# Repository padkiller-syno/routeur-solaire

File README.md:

# Routeur solaire — ESPHome sur ESP32 DevKit V1

Portage du routeur Profes'Solaire v9.15 (`esp32_oled_ac_v9_15.ino`) sur un **ESP32 DevKit V1**
(ESP-WROOM-32) sous **ESPHome**, relié à Home Assistant par l'API native. But : envoyer le surplus solaire dans le
ballon d'eau chaude, et garantir de l'eau chaude le soir.

- Gardé : JSY-MK-194T, **2 dimmers** (même table de pas que la v9.15), relais surplus (sortie 3), relais de marche
  forcée, sonde DS18B20 du ballon (désormais déportée en 433 MHz, voir `sonde-433/`).
- Ajouté : sonde DS18B20 de sécurité sur le radiateur des triacs, détection « ballon chaud », seuils du relais réglables
  depuis HA, anti-légionelle, marche forcée de secours si HA est injoignable.
- Retiré : écran OLED, page web ESP-DASH, topics MQTT `mosquitto/...`, relais Bluetooth (routeur dédié au routage).
- **Deux cœurs** : wifi et pile réseau sur le cœur 0 ; boucle ESPHome (JSY, régulation) sur le cœur 1 ;
  triacs pilotés par une interruption de minuterie matérielle.
- Les marches forcées sont faites par des **automatisations Home Assistant** qui lisent les réglages de l'ESP.

Fichiers :
- `esphome/routeur-solaire.yaml` : configuration ESPHome.
- `esphome/routeur-solaire/routeur.h` : décodage du JSY (avec contrôle du CRC Modbus) et table des pas.
- `test/test_routeur.c` : test hors carte de `routeur.h` (`gcc -Wall -o /tmp/t test/test_routeur.c -lm && /tmp/t`).
- `cablage.svg` : schéma de câblage basse tension (ESP, modules, 3,3 V / 5 V / masse).
- `ha-carte-solaire-ecs.yaml` : carte pour la page « Solaire ECS » de HA (coller en carte « Manuel »).
- `outils/vitesse_port_jsy.ino` : passage du JSY de 4 800 à 38 400 bauds (une seule fois, depuis un ESP32).
- `puissance.svg` : schéma de la partie 230 V (tableau, boîtier près du ballon, contacteur, dimmer, ballon).
- `pcb/` : carte mère KiCad générée par script, fichiers de fabrication JLCPCB (voir `pcb/README-pcb.md`).
- `boitier/` : boîtier imprimé 3D OpenSCAD + STL (voir `boitier/README.md`).

Compilé avec ESPHome 2026.10.2 : RAM ≈ 28 %, flash ≈ 49 %. Premier flash : *⋮ → Install → Manual download → Factory format* dans ESPHome, puis
`esptool --chip esp32 --port /dev/ttyUSB0 --baud 460800 write_flash 0x0 routeur-solaire.factory.bin`
(esptool 4.x d'Ubuntu ; Firefox ne sait pas flasher en USB). Ensuite, mises à jour par le wifi.

## Câblage

| Signal | DevKit V1 | GPIO | Remarque |
|---|---|---|---|
| TX du JSY | RX2 | 16 | UART2 matérielle, pont diviseur R1/R2 sur la carte |
| RX du JSY | TX2 | 17 | |
| Z-C (dimmer 1) | D35 | 35 | entrée seule ; commun aux deux dimmers, Z-C du dimmer 2 non branché |
| PWM dimmer 1 (ballon) | D32 | 32 | |
| PWM dimmer 2 (option) | D33 | 33 | 2e charge ; activer « Sortie 2 active » dans HA |
| Relais marche forcée | D25 | 25 | NC → bobine du contacteur |
| Relais surplus | D26 | 26 | |
| Récepteur 433 MHz SRX882 (DATA) | D4 | 4 | bornier J2 ; reçoit la sonde déportée du ballon (`sonde-433/`) |
| DS18B20 triacs (DAT) | D27 | 27 | bus séparé, bornier J3 |
| Ventilateur 5 V des dimmers | D13 | 13 | MOSFET Q1 de la carte : marche au seuil (45 °C, réglable), arrêt 7 °C plus bas, forcé si la sonde des triacs se tait |

- Aucune broche de démarrage (0, 2, 5, 12, 15) n'est utilisée : rien ne s'active au boot ni pendant un flash USB.
- Les logs passent par le port USB (UART0) et le tableau de bord ESPHome ; le JSY a sa propre UART.
- La sonde des triacs a son propre fil : une panne sur un bus ne fait pas perdre l'autre sonde.
- TX du JSY → RX2 par le pont diviseur de la carte, 1 kΩ (R1, en série) / 2 kΩ (R2, vers la masse) : 5 V × 2/3 = 3,3 V.
  Si le TX du JSY sort déjà du 3,3 V (le mesurer au repos), remplacer R1 par un pont de soudure et retirer R2.
- 5 V : alimentation Mean Well IRM-05-5 dans le boîtier → bornier J4 de la carte → VIN de l'ESP, JSY, relais, ventilateur.
  3,3 V (dimmers, sondes) pris sur la broche 3V3 de l'ESP ; masse commune.

### Matériel

- **JSY-MK-194T déjà passé à 38 400 bauds** par `outils/vitesse_port_jsy.ino` (croquis ESP32 : requête Modbus en
  diffusion, registre 0x0004 = 0x0108, soit adresse 1 et code vitesse 8 = 38 400). C'est la vitesse et l'adresse
  qu'attend ESPHome ; c'est aussi la vitesse maximale du JSY, à garder (≈ 18 ms par échange, contre ≈ 144 ms à
  4 800 bauds, plus que le cycle de 120 ms). Un JSY neuf ou remis à zéro est à 4 800 bauds : bouton
  « JSY : passer à 38 400 bauds » dans HA (diagnostics de l'appareil, **masqué par défaut** : l'activer d'abord). Il
  coupe le dimmer, envoie la trame de réglage à 4 800 puis à 9 600 bauds, revient à 38 400 et écrit dans les logs si
  les mesures sont revenues. Le croquis reste utile sans ESPHome.
- **JSY-MK-194T** : broches VCC, RX, TX, PF, GND (PF non branchée). Canal 1 = tore intégré, à faire traverser par le fil
  du ballon ; canal 2 = pince externe sur l'arrivée générale ; UL/NL = 230 V pour la mesure de tension.
- **Sonde DS18B20 des triacs** (VCC, DAT, GND) sur le bornier J3, en 3,3 V : la résistance de tirage 4,7 kΩ est sur la
  carte (R4), ne pas en ajouter.
- **Sonde du ballon déportée** : le routeur est près du tableau, à ~10 m du ballon, et 10 m de câble 1-Wire le long de
  l'alimentation du ballon donnent des lectures fausses. Elle est lue sur place par un Pro Mini sur 18650 qui l'envoie en
  433 MHz (`sonde-433/README.md`). Récepteur **SRX882** sur J2 : VCC → 3,3 V, DATA → DAT, GND, **CS → 3,3 V**, antenne
  de 17,3 cm hors du tableau métallique. Entités `Batterie sonde ballon` et `Sonde ballon` (connectivité).
- **Ballon : 8 A (≈ 1 850 W)**, circuit dédié au tableau : différentiel 30 mA → disjoncteur 16 A → câble 3G 2,5 mm²
  jusqu'au ballon. Raccordement par une sortie de câble puis les presse-étoupes du boîtier, **pas de prise** (une prise
  chauffe sous une charge résistive de plusieurs heures par jour).
- **Relais : modules 5 V 10 A à déclenchement bas** (Songle SRD-05VDC-SL-C, broches IN / GND / VCC, bobine ≈ 70 mA),
  enfichés sur K1 (marche forcée) et K2 (surplus).
  - Relais surplus : contact NO vers une charge annexe de 2 kW au plus (au-delà, passer par un contacteur).
  - Relais marche forcée : il ne coupe pas le ballon lui-même, il pilote la **bobine du contacteur** par son
    contact **NC** : COM ← L, NC → A1 du contacteur, A2 → N. ESP éteint ou en panne = relais au repos = contacteur
    collé = ballon en direct sur son thermostat. En routage, la bobine du petit relais est alimentée en permanence.
  - Réglages pour ces modules, à poser dans `substitutions` au montage : `relais_surplus_inverse: "true"`,
    `relais_mf_inverse: "false"` (le fichier a encore les valeurs d'un module à déclenchement haut, l'inverse).
  - **Piège** : alimentés en 5 V, ces modules peuvent ne pas décoller avec les 3,3 V de l'ESP (pour leur transistor,
    3,3 V est encore un niveau bas). Test au banc avant montage : IN à la masse → le relais colle ; IN en l'air → il
    doit décoller franchement. S'il reste collé avec la broche de l'ESP à 3,3 V : passer les sorties en `open_drain`,
    ou souder une diode 1N4148 en série sur IN (cathode côté ESP).
- **Contacteur jour/nuit AEG 666120** (20 A, 2 NO, bobine 230 V, commutateur 0 / AUTO / 1) : sur rail DIN près du
  ballon. Son contact de puissance relie L à la phase du ballon, en parallèle de la sortie LOAD du dimmer : en marche
  forcée, le triac est court-circuité. Commutateur sur **AUTO** ; **1** = marche forcée manuelle, même ESP en panne ;
  **0** = ballon coupé.
- **Pince du canal 2 (arrivée générale), rallongée jusqu'au tableau** — le boîtier est près du ballon :
  - Câble : **H05VV-F 2 × 0,75 mm²** (isolé 300/500 V), torsadé à la main (un tour tous les 5 à 10 cm), ou sa version
    blindée (blindage relié à la masse côté JSY seulement). Une pince à sortie courant supporte sans souci 10 à 20 m.
  - Passage : dans la même gaine ICTA que le câble du ballon, ou fixé le long d'elle. Les fils de la pince sont reliés
    au circuit de mesure du JSY, référencé au secteur : les traiter comme du 230 V (pas de câble Ethernet).
  - Raccord : souder et gainer (thermorétractable), ou bornier dans une boîte ; garder la fiche d'origine côté JSY.
  - **Ne jamais laisser la pince fermée sur un câble sous tension avec ses fils débranchés** (secondaire de
    transformateur de courant ouvert = tension élevée, pince abîmée) : brancher d'abord la rallonge, puis clipser.
  - Pose : autour de la **phase seule** de l'arrivée générale, après le compteur et avant tous les départs.
    Flèche de la pince dans le sens compteur → maison.
  - Contrôle : la nuit (aucune production), `Puissance réseau` doit être **positive** dans HA. Si elle est
    négative, retourner la pince.
- **Alimentation 5 V** : Mean Well IRM-05-5 (5 V 1 A, classe II) dans le boîtier, derrière un fusible **T1A** temporisé
  sur la phase (porte-fusible de façade 250 V) ; le même fusible protège les fils L/N du JSY. Sortie sur J4 (bornier
  débrochable 2 points, pas de 3,5 mm), protégée sur la carte par F1 (PTC 1,1 A) et D2. ≈ 0,6 A en pointe (ESP32 avec
  wifi, JSY, 2 relais, ventilateur). Le micro-USB de l'ESP ne sert plus qu'au premier flash.
- **Dimmer RobotDyn « AC Dimmer Module HL » 16/24 A 600 V** : logique VCC (3,3 V),
  GND, Z-C → D35, PWM → D32 (dimmer 2 : PWM → D33, Z-C libre). Puissance : AC-IN **L** et **N**, sortie **LOAD** vers la phase du ballon ; l'autre fil du
  ballon va directement au neutre. Avec un ballon de 8 A, la version 16 A est à l'aise (≈ 10 W dans le triac) ;
  radiateur à l'air libre, sonde DS18B20 « triacs » collée (pâte ou colle thermique) sur le peigne en aluminium, au plus
  près du triac (avec deux dimmers : sur celui qui chauffe le plus, ou les deux radiateurs serrés l'un contre l'autre).
- Sonde du ballon : en partie haute (doigt de gant ou contre la cuve sous l'isolant), c'est l'eau qui sort au robinet.

## Installation

1. Copier `esphome/routeur-solaire.yaml` et le dossier `esphome/routeur-solaire/` dans la configuration ESPHome.
2. Ajouter à `secrets.yaml` : `wifi_ssid`, `wifi_password`, `routeur_api_key` (clé de 32 octets en base64, par exemple
   `openssl rand -base64 32`) et `routeur_ota_password`.
3. Premier flash par USB (voir plus haut), puis mises à jour par le wifi.
4. Dans HA : *Paramètres → Appareils et services → Ajouter une intégration → ESPHome* (découverte automatique sur le
   même réseau, sinon par l'IP de l'ESP, port 6053), avec la clé d'API. Réserver l'IP de l'ESP dans le DHCP de la box.
5. Créer les automatisations de marche forcée (voir *Fonctionnement*) et le capteur `statistics`
   `sensor.ballon_temperature_max_7_jours` (max sur 7 jours de la température du ballon).
6. Carte de tableau de bord : *Ajouter une carte → Manuel* → coller `ha-carte-solaire-ecs.yaml`.

Réglages dans `substitutions` : `dimmer_max` (95 %), `mf_duree_max` (la marche forcée se coupe seule au bout de 8 h si
HA ne l'a pas fait), `triac_coupure` / `triac_reprise` (75 / 60 °C).

## Fonctionnement

**Routage** (dans l'ESP, toutes les 120 ms) : une consigne unique monte ou descend selon la puissance réseau pour
viser entre −30 et 0 W d'injection, avec la table de pas de la v9.15. De 0 à 95 % elle pilote le dimmer 1 (ballon) ;
au-delà, si « Sortie 2 active » est allumé, le dimmer 2 prend la suite jusqu'à 95 %. À la descente, le dimmer 2 baisse
d'abord, puis le dimmer 1 : pas d'à-coup (la v9.15 remettait la sortie 2 à zéro dès que la 1 quittait son maximum).
« Sortie 2 active » est éteint par défaut : ne l'allumer qu'avec une charge branchée sur le dimmer 2.
Le JSY ne rafraîchit ses mesures que toutes les 330 ms : la consigne n'est corrigée que sur une trame nouvelle
(la v9.15 appliquait le même pas 2 à 3 fois sur la même mesure). 5 s de trames identiques = JSY figé, traité comme muet
(dimmer coupé). Wifi coupé : l'ESP ne redémarre jamais et continue de router seul.

**Marche forcée de secours** : si HA est injoignable à l'heure réglée, l'ESP applique seul la règle « température »
(chauffe si l'eau est sous la consigne, arrêt dès qu'elle l'atteint), avec l'heure de HA ou à défaut l'heure Internet
(SNTP). Quand HA est là, l'ESP le laisse faire.

**Relais surplus** : collé quand surplus (injection + puissance du ballon) > « seuil marche », décollé sous
« seuil arrêt », au moins 60 s entre deux changements. Les deux seuils se règlent dans HA (1000 / 800 W par défaut) :
mettre le seuil de marche à peu près à la puissance de la charge branchée sur ce relais.

**Ballon chaud** : dimmer au maximum mais moins de 30 W dans le ballon pendant 60 s = thermostat du ballon ouvert.
`binary_sensor.sdb_routeur_solaire_ballon_chaud` passe à « on » (levé dès que le ballon reprend plus de 100 W). Le surplus
n'a alors plus que le relais surplus ; le capteur peut aussi servir dans HA (notification, lancer un appareil…).

**Sécurité triac** : radiateur ≥ 75 °C → dimmer coupé, reprise sous 60 °C. Sonde absente ou muette depuis 60 s →
dimmer coupé aussi (sûr par défaut : **sans cette sonde branchée, le routeur ne route pas**). La marche forcée n'est
pas concernée (elle passe par le contacteur, pas par le triac). `binary_sensor.sdb_routeur_solaire_securite_triac`
signale le problème.

**Marches forcées** (automatisations HA, à l'heure réglée sur l'ESP) :

| Automatisation | Quand | Arrêt |
|---|---|---|
| marche forcée température (activée par défaut) | à 16:00 si l'eau est sous 40 °C | dès que l'eau dépasse 40 °C |
| anti-légionelle | à 16:00 si l'eau n'a pas dépassé 60 °C depuis 7 jours | à 60 °C, ou au bout de 6 h |
| marche forcée volume (désactivée par défaut) | à l'heure réglée, si l'énergie routée du jour est sous le besoin du ballon (formules v9.15) | après la durée calculée |

- 16:00 et 40 °C sont les valeurs par défaut de l'ESP, modifiables dans HA ; elles servent à toutes les marches forcées.
- Pendant l'anti-légionelle, l'arrêt à 40 °C de la marche forcée température est suspendu.
- Le max sur 7 jours vient de `sensor.ballon_temperature_max_7_jours` (intégration `statistics`, `configuration.yaml`).
  Juste après la mise en service, il n'a que quelques heures d'historique : un premier cycle à 60 °C est normal.
- Sans sonde du ballon (aucune trame reçue depuis 5 min), ni marche forcée température ni anti-légionelle (la v9.15 lisait −127 °C et chauffait toutes
  les nuits).
- Si HA redémarre pendant une marche forcée volume ou anti-légionelle, l'arrêt est perdu : la sécurité de 8 h de l'ESP coupe.

## Entités Home Assistant

HA préfixe les entités par la pièce de l'appareil (ici `sdb_`, salle de bain) : adapter les noms ci-dessous, les
automatisations et la carte à votre installation.

**Commandes et réglages** (gardés dans la flash de l'ESP, ils survivent aux coupures) :

| Entité | Défaut | v9.15 |
|---|---|---|
| `switch.sdb_routeur_solaire_marche_forcee` | arrêt | bouton « Auto / Marche forcée » (inversé) |
| `switch.sdb_routeur_solaire_programmation_temperature` | marche | « Horloge On/Off température » |
| `switch.sdb_routeur_solaire_programmation_volume` | arrêt | « Horloge On/Off volume » |
| `time.sdb_routeur_solaire_heure_marche_forcee` | 16:00 | curseurs heure / minute |
| `number.sdb_routeur_solaire_temperature_marche_forcee` | 40 °C (10-90, pas de 5) | curseur température |
| `number.sdb_routeur_solaire_volume_ballon` | 200 L | `volume` dans le code |
| `number.sdb_routeur_solaire_relais_surplus_seuil_marche` | 1000 W | `relayOn` dans le code |
| `number.sdb_routeur_solaire_relais_surplus_seuil_arret` | 800 W | `relayOff` dans le code |

**Mesures** — elles remplacent les capteurs du bloc `mqtt:` (l'historique reste sur les anciennes entités) :

| Entité | Ancien capteur MQTT |
|---|---|
| `sensor.sdb_routeur_solaire_puissance_reseau` (W, > 0 soutirage, < 0 injection) | « Consommation » |
| `sensor.sdb_routeur_solaire_puissance_ballon` (W) | « Puissance surplus » |
| `sensor.sdb_routeur_solaire_energie_routee` (kWh, utilisable dans le tableau Énergie) | « Energie sauvée totale » |
| `sensor.sdb_routeur_solaire_energie_reseau_canal_2` (kWh) | « Consommation Enedis totale » |
| `sensor.sdb_routeur_solaire_energie_routee_aujourd_hui` (kWh depuis 4h30 ou le démarrage) | « Energie sauvée aujourd'hui » |
| `sensor.sdb_routeur_solaire_temperature_ballon` (°C, toutes les 30 s) | « Température ballon » |

Nouveaux : `sensor.sdb_routeur_solaire_injection_reseau` (W partis sur le réseau, pince du canal 2),
`sensor.sdb_routeur_solaire_energie_injectee` (kWh, calculée dans l'ESP, gardée en flash : « Retour au réseau » du
tableau Énergie), `sensor.sdb_routeur_solaire_sortie_dimmer` (%), `sensor.sdb_routeur_solaire_temperature_triac` (diagnostic),
`binary_sensor.sdb_routeur_solaire_ballon_chaud`, `…_securite_triac`, `…_relais_surplus`, `…_relais_marche_forcee`,
`…_mesure_jsy` (déconnecté si aucune trame valide depuis 3 s : dimmer coupé), `sensor.ballon_temperature_max_7_jours` (HA).

## Différences avec la v9.15

- Trames JSY vérifiées (longueur, en-tête, CRC). La v9.15 décodait n'importe quoi : une trame tronquée donnait une
  puissance fausse et un saut du dimmer. Sans trame valide pendant 3 s, le dimmer est coupé.
- À 0 W pile, la v9.15 reprenait le pas précédent (aucune condition ne couvrait 0) : ici, pas = 0.
- Dimmer : composant `ac_dimmer` d'ESPHome au lieu de RBDdimmer. La courbe % → angle de phase peut différer un peu ;
  la régulation étant en boucle fermée, ça ne change que la vitesse de convergence.
- Heure fournie par HA (heure d'été comprise ; la v9.15 restait en UTC+1 toute l'année).
- Marche forcée par défaut à 16:00 sous 40 °C (pour l'eau du soir) au lieu de 01:30 sous 50 °C.

## Reste à vérifier sur la carte

- Boot normal avec tout le câblage branché.
- Valeurs du JSY cohérentes dans HA (tension ~230 V, signe de la puissance réseau).
- Dimmer qui suit le surplus sans osciller. Sinon, réduire les pas dans `routeur.h` ou monter l'intervalle de 120 ms.
- Sens du zéro crossing : si le dimmer scintille ou reste éteint, essayer `inverted: true` sur `zero_cross_pin`.
- « Ballon chaud » qui passe bien à « on » quand le thermostat coupe (ballon à 0 W, dimmer à 95 %).
- Température du triac en plein soleil (8 A pendant des heures) : elle doit rester nettement sous 75 °C.
- Relais marche forcée : ESP débranché → le contacteur colle ; ESP en routage → il décolle.
- Relais à déclenchement bas : chacun décolle bien quand l'ESP relâche sa sortie (voir *Matériel*).

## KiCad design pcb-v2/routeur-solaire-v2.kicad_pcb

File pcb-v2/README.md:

# Carte v2 du routeur solaire (compacte, < 100 × 100 mm)

Variante de la carte v1 (`../pcb/`) pour réduire le prix chez JLCPCB : la carte ne passe que sous **l'ESP32 et les
barrettes des modules**. Chaque module reste enfiché directement (aucun câble basse tension) ; la partie qui déborde
de la carte repose sur des **supports imprimés** du boîtier (`../boitier-v2/` : appuis, plot à vis, crochets souples).

- Carte **99,1 × 92,1 mm**, 2 couches, mêmes 13 composants CMS que la v1 (assemblage JLCPCB Economic, mêmes
  références LCSC) et mêmes connecteurs à souder (barrettes femelles, borniers au pas de 3,5 mm, barrette ventilateur).
- Contrôle KiCad : **0 erreur, 0 liaison manquante** (remarques de sérigraphie seulement).
- Plus aucun 230 V au-dessus de la carte, sauf la bande basse tension des modules : seul le bord « commande » des
  dimmers (12 mm), la bande de J3 du JSY et l'extrémité VCC/GND/IN des relais surplombent la carte.

Disposition (repère de l'intérieur du boîtier, comme la v1) :
- dimmers côte à côte au fond (borniers vers la paroi arrière), barrettes sur le bord haut de la carte ;
- JSY debout à droite des dimmers, **tourné de 180° par rapport à la v1** (J3 à gauche sur la languette de la carte,
  tore en bas, L/N dans le coin bas-droit) ;
- relais couchés à droite, borniers NO/COM/NC vers la paroi droite ;
- ESP32 au centre, micro-USB vers la paroi gauche ; borniers des sondes et du 5 V sur le bord avant.

Fichiers : `genere_pcb.py` (placement), `route_pcb.py` (Freerouting + plans de masse), `exporte.sh` (Gerber, CPL,
rendu, PDF 1:1), `routeur-solaire-v2-jlcpcb.zip`, `jlcpcb-bom.csv`, `jlcpcb-cpl.csv`, `rendu-3d.png`,
`placement-1-1.pdf`.

**Non testée** : à valider par une impression 1:1 avec les modules posés dessus avant commande, comme la v1.
Commande : même procédure que `../pcb/README-pcb.md` (finition HASL, Economic, C3 = C2992615).

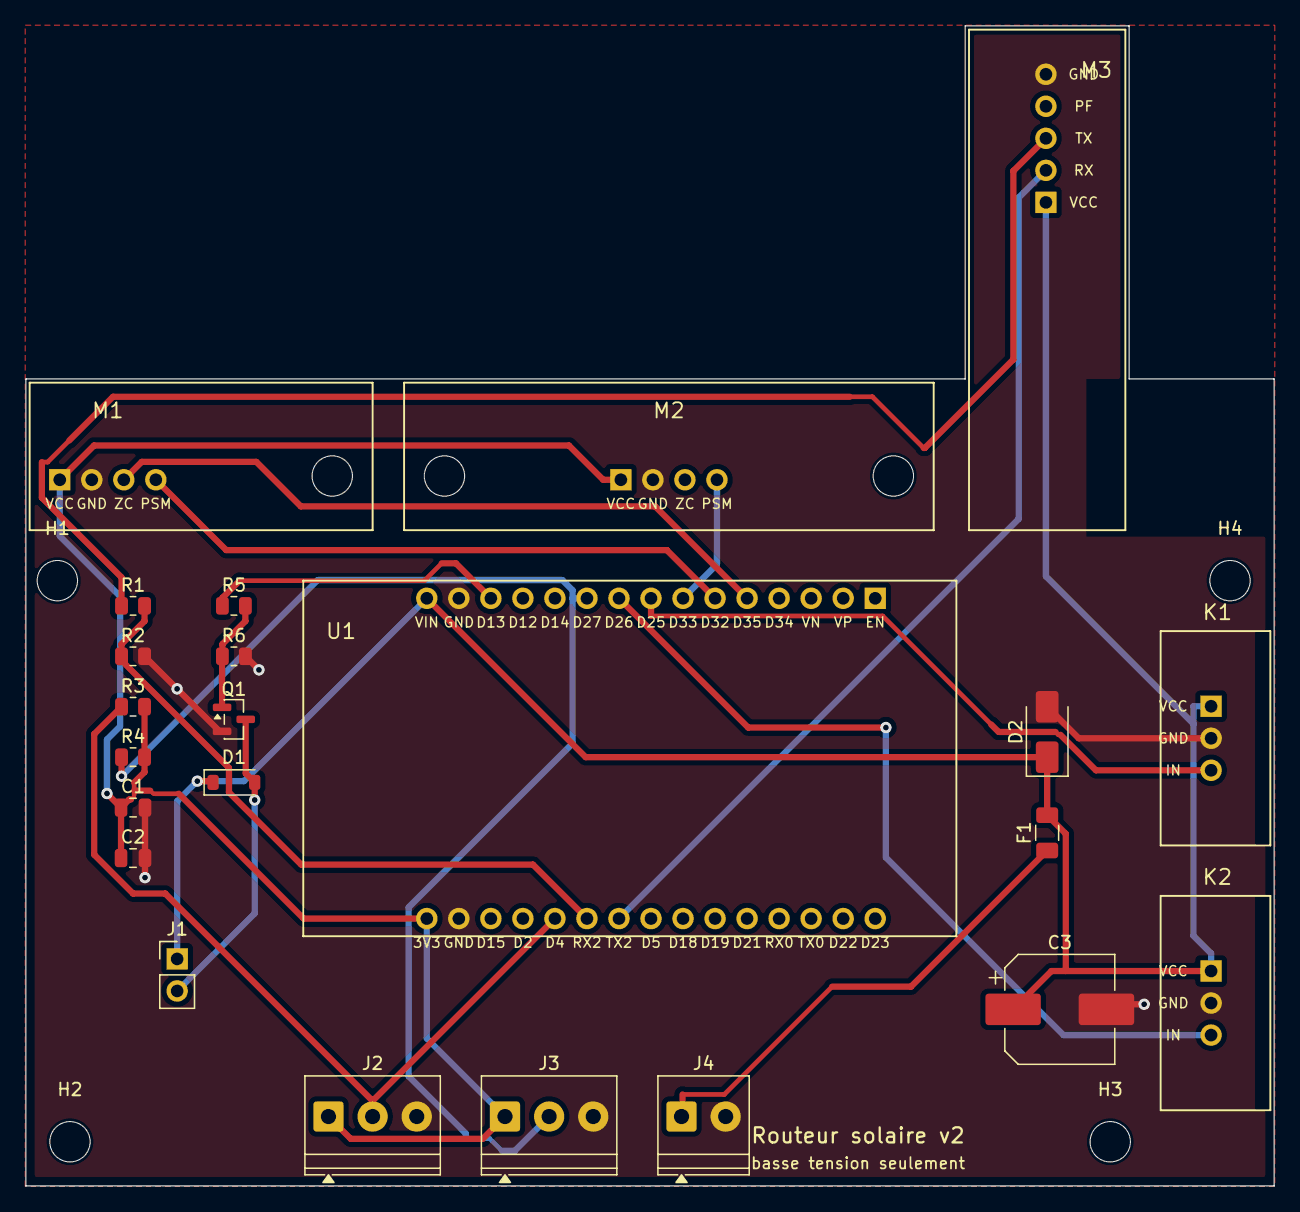
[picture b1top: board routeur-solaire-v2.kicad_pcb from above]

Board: 2 copper layers, 99.0 x 92.0 mm, 27 parts (0 on the bottom side), 17 nets.

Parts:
C1, C2: 100n; C_0805_2012Metric
C3: 470uF 16V; CP_Elec_8x10.5
D1: 1N4148W; D_SOD-123
D2: SS14; D_SMA
F1: PTC 1,1 A 6 V; Fuse_1206_3216Metric
H1, H2, H3, H4: M3; MountingHole_3.2mm_M3
J1: Ventilateur 5 V; PinHeader_1x02_P2.54mm_Vertical
J2: Sonde ballon (VCC DAT GND); TerminalBlock_Phoenix_PT-1,5-3-3.5-H_1x03_P3.50mm_Horizontal
J3: Sonde triacs (VCC DAT GND); TerminalBlock_Phoenix_PT-1,5-3-3.5-H_1x03_P3.50mm_Horizontal
J4: Alim 5 V (+ / GND); TerminalBlock_Phoenix_PT-1,5-2-3.5-H_1x02_P3.50mm_Horizontal
K1: Relais MF (NC → contacteur); Module_K1
K2: Relais surplus; Module_K2
M1: Dimmer 1 (ballon) RobotDyn HL; Module_M1
M2: Dimmer 2 (option) RobotDyn HL; Module_M2
M3: JSY-MK-194T; Module_M3
Q1: AO3400A; SOT-23
R1, R5: 1k; R_0805_2012Metric
R2: 2k; R_0805_2012Metric
R3, R4, R6: 4k7; R_0805_2012Metric
U1: ESP32 DevKit V1 (30 broches); Module_U1

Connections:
+3V3: C1.1, C2.1, J2.1, J3.1, M1.1, M2.1, R3.2, R4.2, U1.30
+5V: C3.1, D1.1, D2.1, F1.2, J1.1, K1.1, K2.1, M3.1, U1.15
+5V_EXT: F1.1, J4.1
DS_BALLON: J2.2, R3.1, U1.26
DS_TRIACS: J3.2, R4.1, U1.10
GND: C1.2, C2.2, C3.2, D2.2, J2.3, J3.3, J4.2, K1.2, K2.2, M1.2, M2.2, M3.5, Q1.2, R2.2, R6.2, U1.14, U1.29
JSY_TX: M3.3, R1.1
PWM1: M1.4, U1.6
PWM2: M2.4, U1.7
REL_MF: K1.3, U1.8
REL_SURPLUS: K2.3, U1.9
RX2: R1.2, R2.1, U1.25
TX2: M3.2, U1.24
VENTILO_CMD: R5.1, U1.13
VENTILO_G: Q1.1, R5.2, R6.1
VENTILO_NEG: D1.2, J1.2, Q1.3
ZC: M1.3, U1.5
